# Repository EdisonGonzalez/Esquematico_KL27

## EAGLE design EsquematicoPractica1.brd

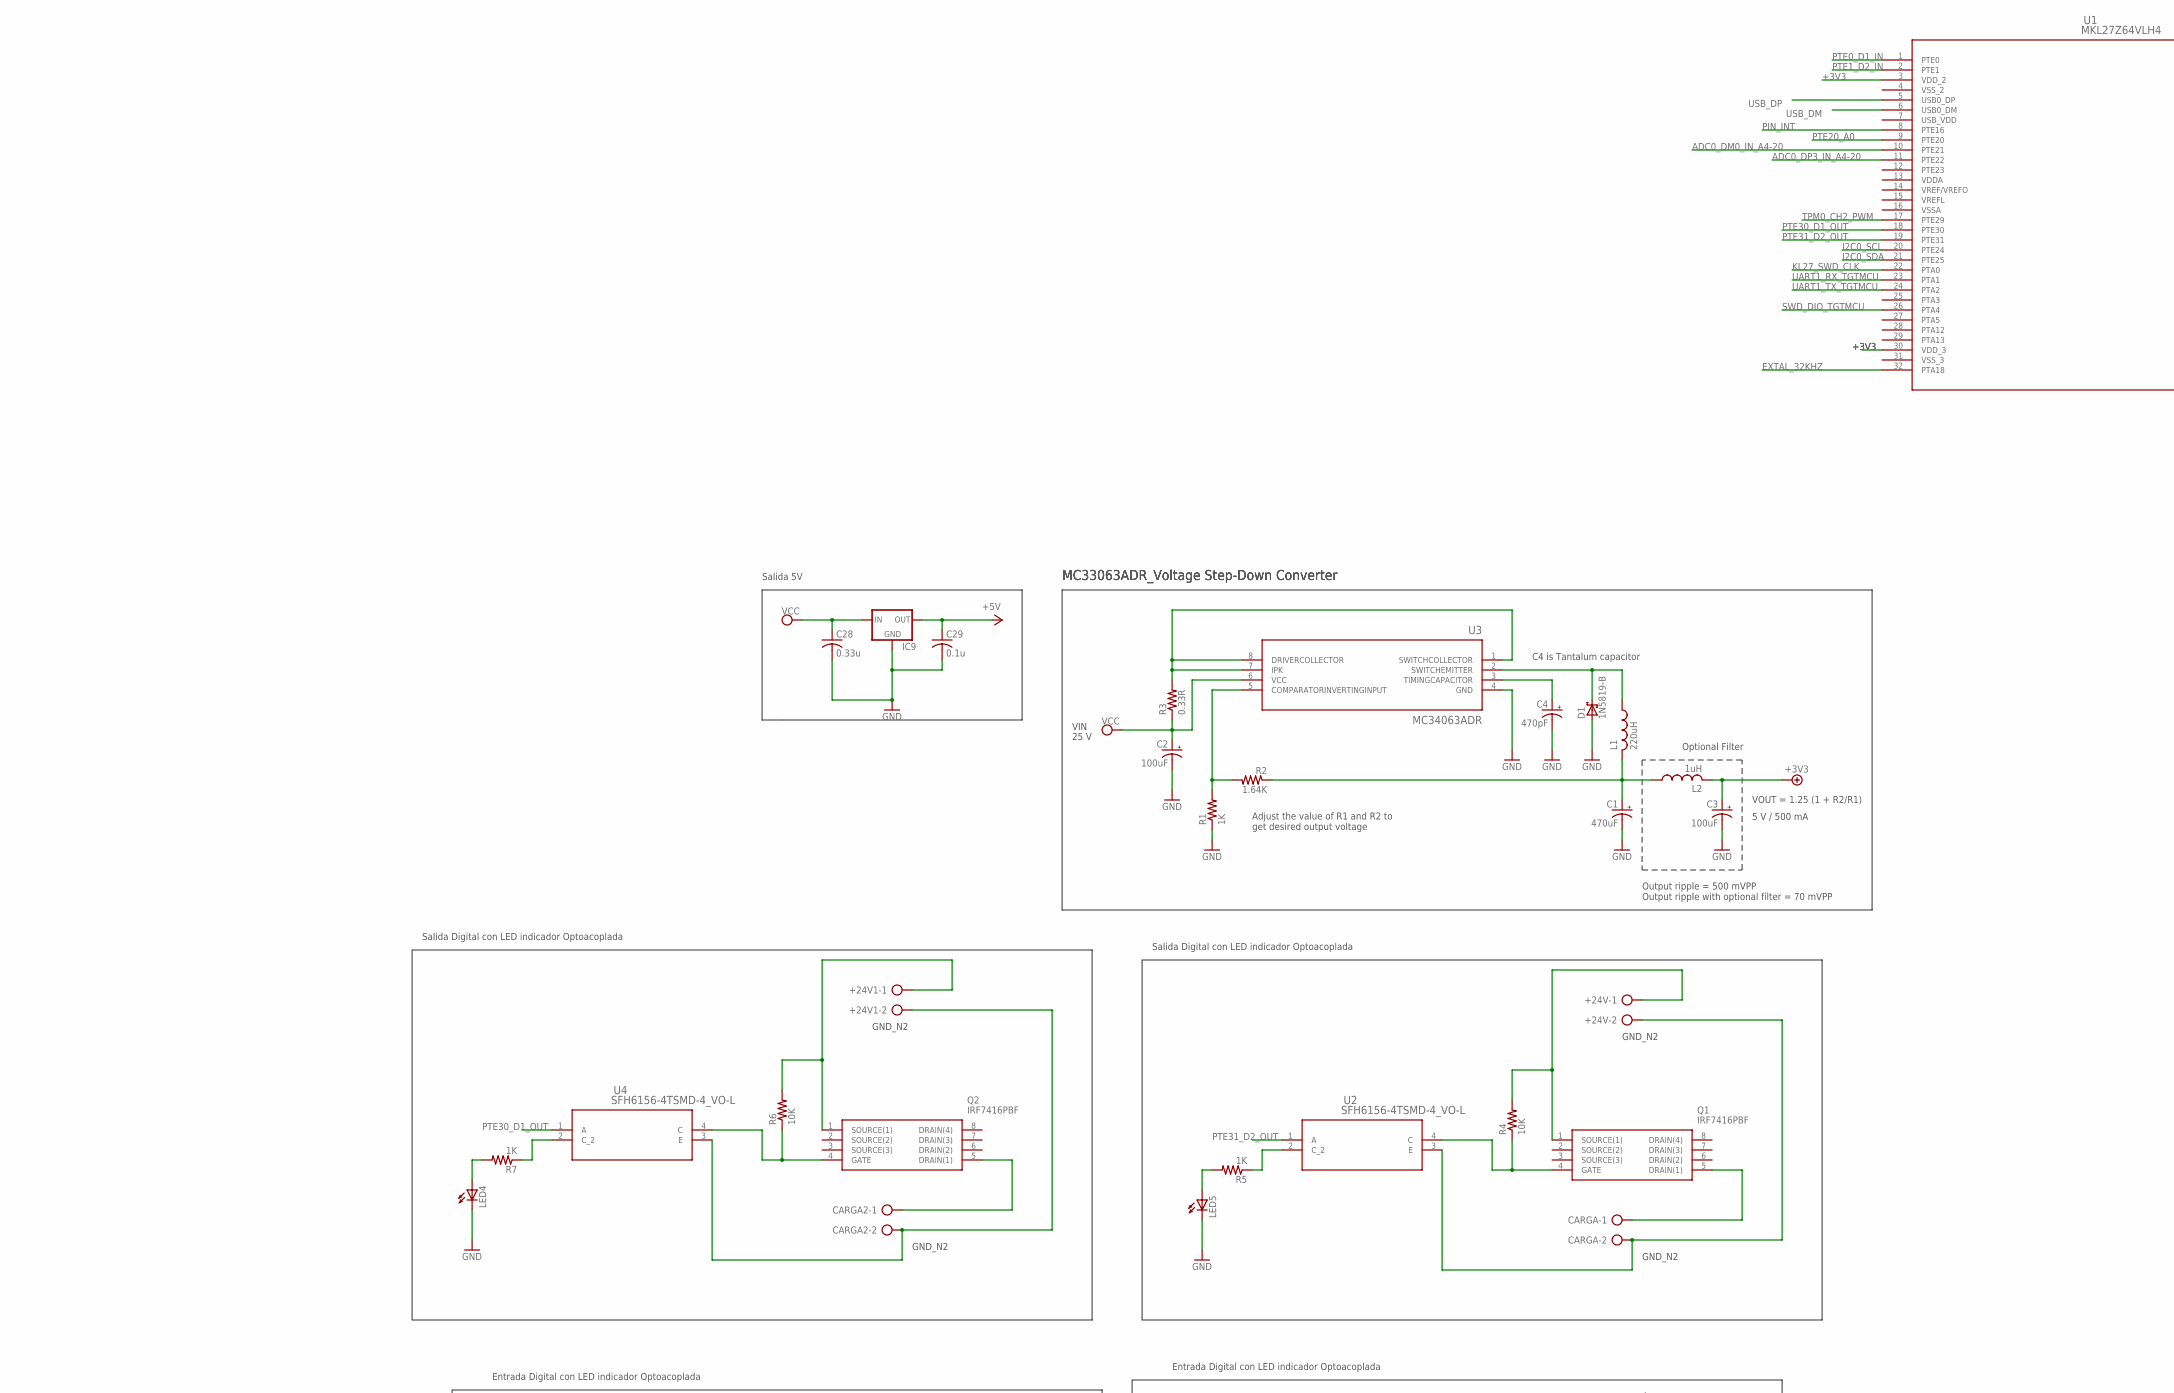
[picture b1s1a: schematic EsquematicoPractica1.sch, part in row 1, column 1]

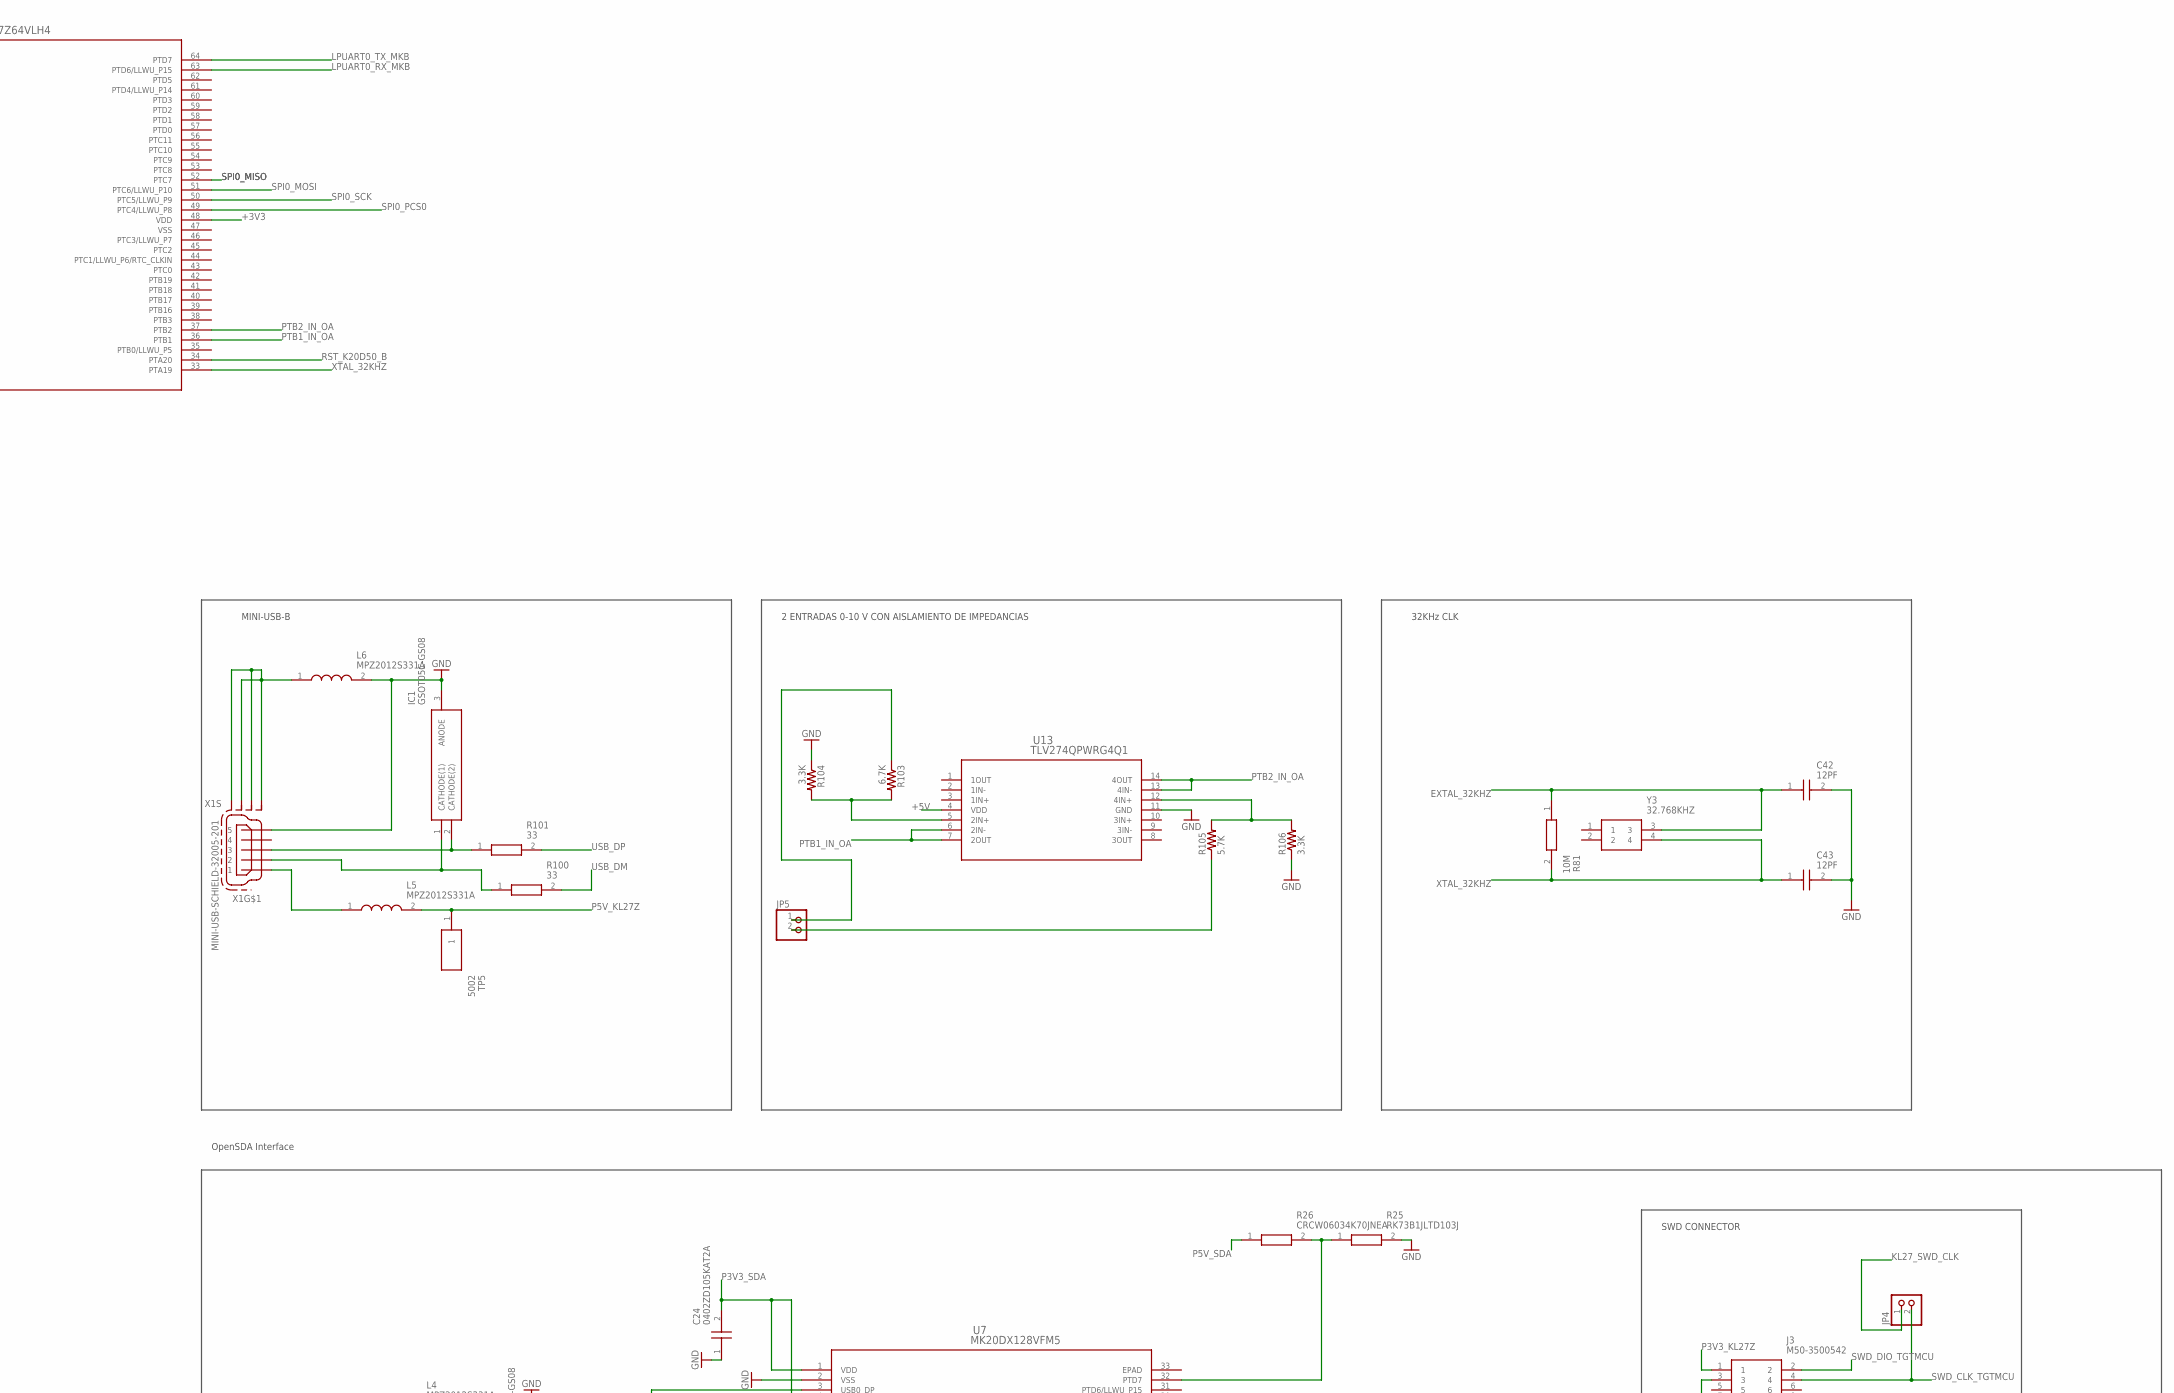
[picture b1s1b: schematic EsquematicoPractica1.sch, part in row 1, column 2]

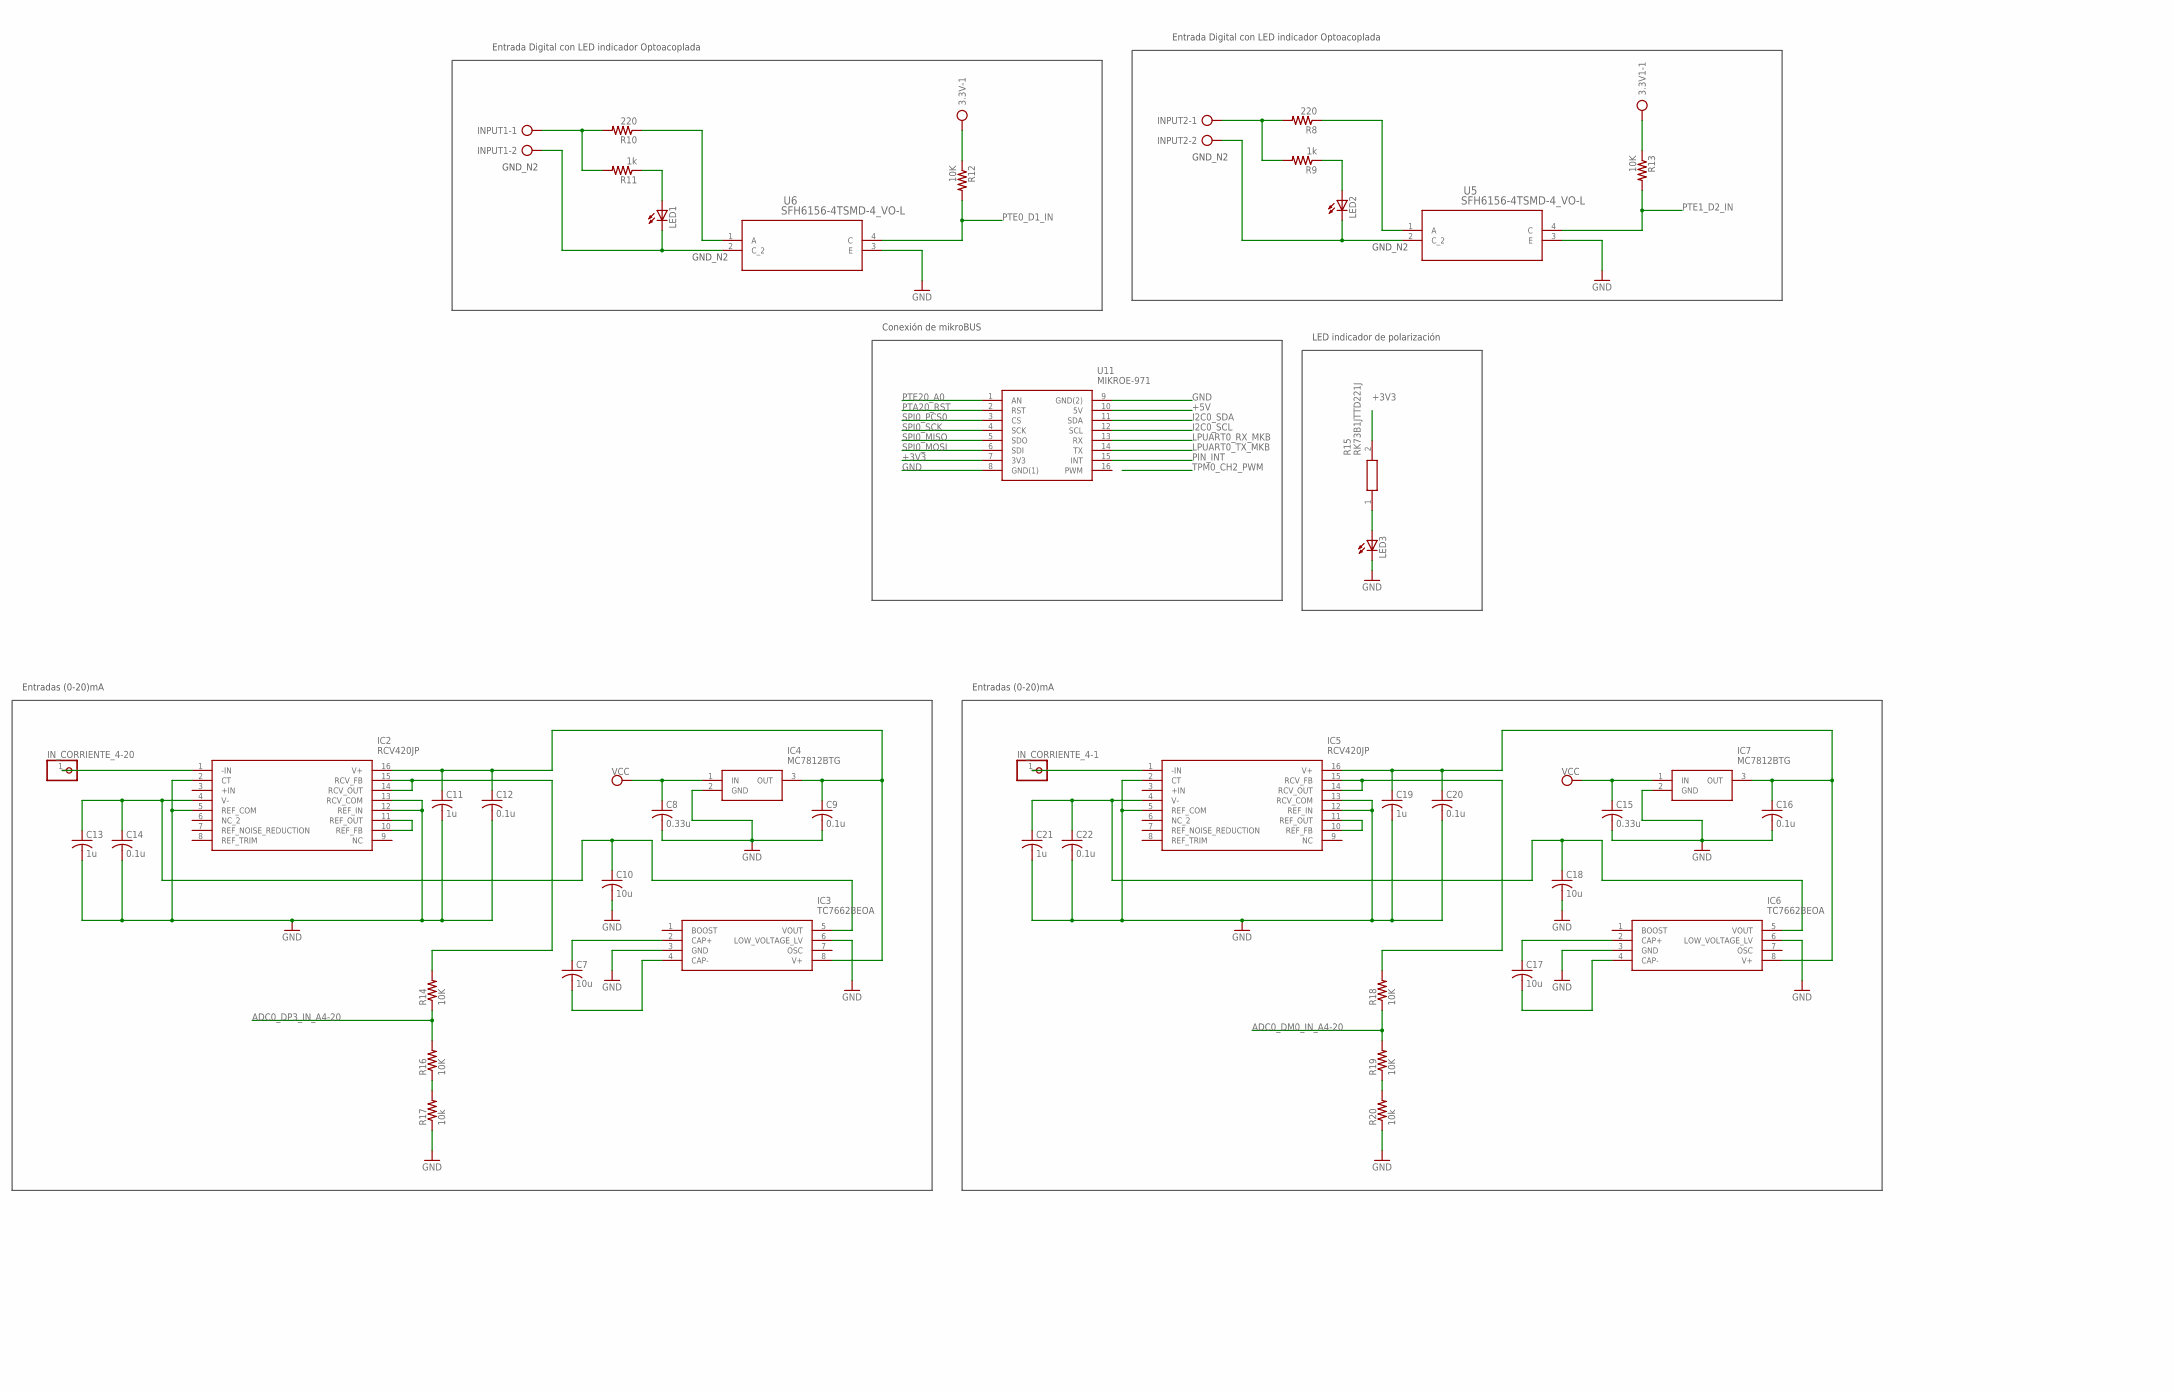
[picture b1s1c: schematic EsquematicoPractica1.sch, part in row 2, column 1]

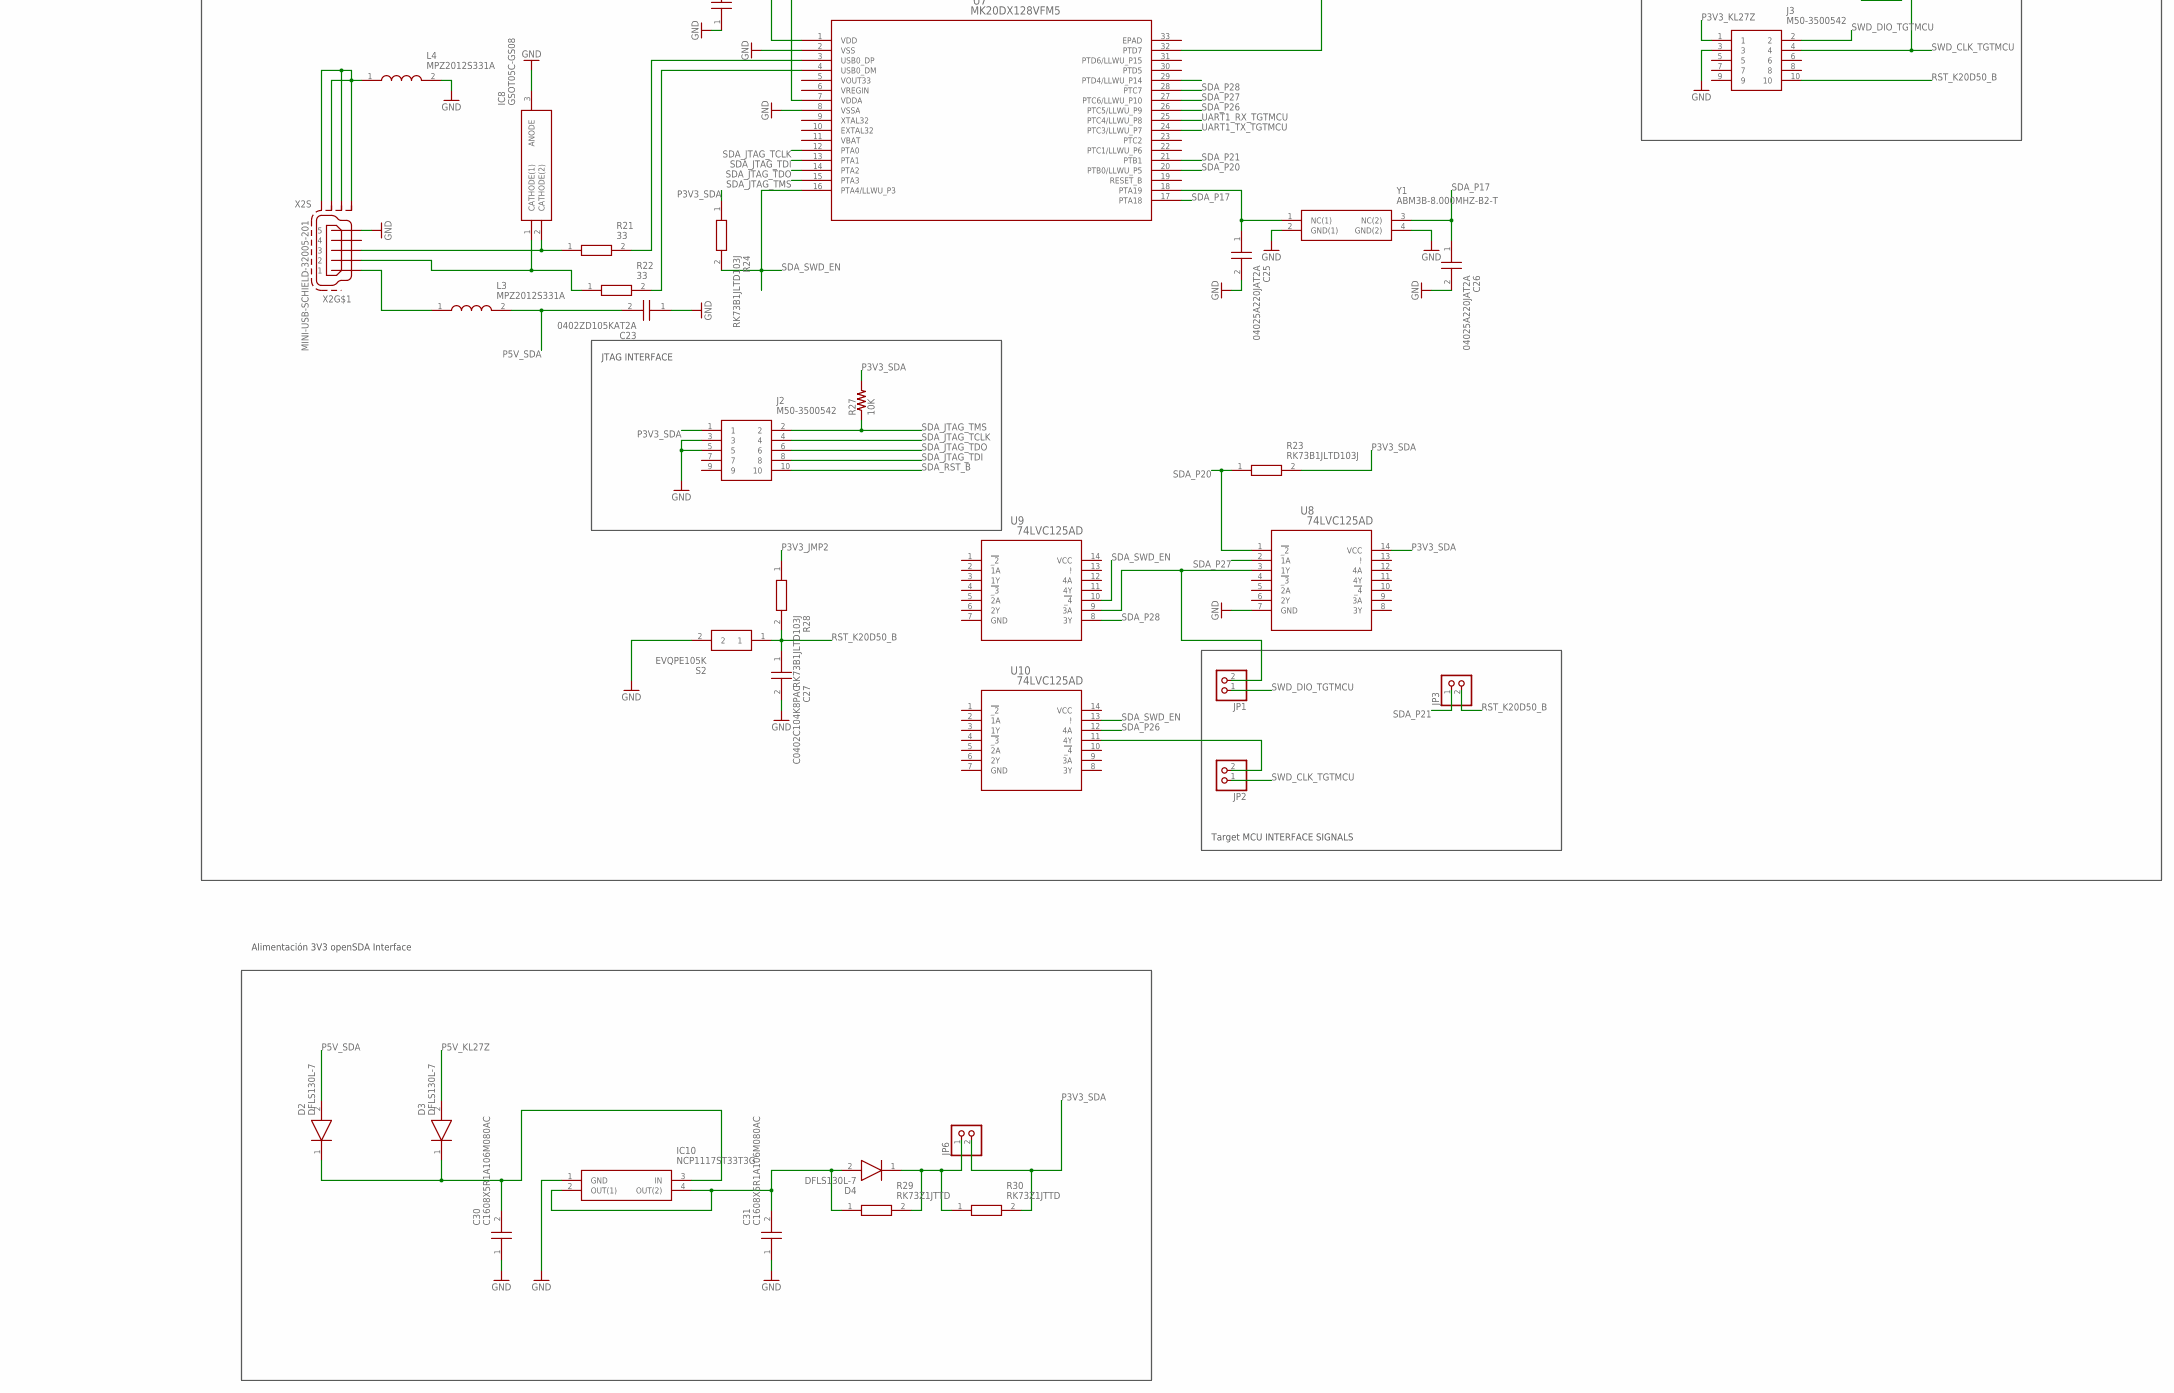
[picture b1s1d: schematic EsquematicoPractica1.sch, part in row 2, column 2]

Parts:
3.3V, 3.3V1: AK300/2
+24V, +24V1: AK300/2
C1: 470uF; E7,5-16
C2, C3: 100uF; E2,5-6E
C4: 470pF; E2,5-6E
C7, C10, C17, C18: 10u; C0805
C8, C15, C28: 0.33u; C0805
C9, C12, C14, C16, C20, C22, C29: 0.1u; C0805
C11, C13, C19, C21: 1u; C0805
C23, C24: 0402ZD105KAT2A; CAPC1005X56N
C25, C26: 04025A220JAT2A; CAPC1005X56N
C27: C0402C104K8PAC; CAPC1005X55N
C30, C31: C1608X5R1A106M080AC; CAPC1608X80N
C42, C43: 12PF; CAPC1005X55N
CARGA, CARGA2: AK300/2
D1: 1N5819-B; DO41-7.6
D2, D3, D4: DFLS130L-7; POWERDI_123
IC1, IC8: GSOT05C-GS08; SOT95P248X115-3N
IC2, IC5: RCV420JP; DIP254P762X508-16
IC3, IC6: TC7662BEOA; SOIC127P600X175-8N
IC4, IC7: MC7812BTG; TO254P482X997X2018-3P
IC9: 78XXL
IC10: NCP1117ST33T3G; SOT230P700X180-4N
INPUT1, INPUT2: AK300/2
IN_CORRIENTE_4-1, IN_CORRIENTE_4-20: PINHD-1X1; 1X01
J2, J3: M50-3500542; HDRV10W40P127_2X5_635X345X415P
JP1, JP2, JP3, JP4, JP6: PINHD-1X2/90; 1X02/90
JP5: PINHD-1X2; 1X02
L1: 220uH; L3216C
L2: 1uH; L3216C
L3, L4, L5, L6: MPZ2012S331A; INDC2012X105N
LED1, LED2, LED3, LED4, LED5: LED5MM
Q1, Q2: IRF7416PBF; SOIC127P600X175-8N
R1: 1K; M0805
R2: 1.64K; M0805
R3: 0.33R; M0805
R4, R6: 10K; 0309/12
R5, R7: 1K; 0309/12
R8: 220; 0309/12
R9, R11: 1k; 0309/12
R10: 220; 0204/7
R12, R13: 10K; 0204/7
R14, R16, R18, R19: 10K; M0805
R15: RK73B1JTTD221J; RESC1608X55N
R17, R20: 10k; M0805
R21, R22, R100, R101: 33; RESC1005X40N
R23, R24, R25, R28: RK73B1JLTD103J; RESC1608X55N
R26: CRCW06034K70JNEA; RESC1608X50N
R27: 10K; M1206
R29, R30: RK73Z1JTTD; RESC1608X55N
R81: 10M; RESC1608X55N
R103: 6.7K; M1206
R104, R106: 3.3K; M1206
R105: 5.7K; M1206
S2: EVQPE105K; EVQPE1
TP5: 5002
U1: MKL27Z64VLH4; 98ASS23234W
U2, U4, U5, U6: SFH6156-4TSMD-4_VO-L; SMD-4_VO-L
U3: MC34063ADR; D8
U7: MK20DX128VFM5; QFN-32_5X5X0.9
U8, U9, U10: 74LVC125AD; SOT108-1
U11: MIKROE-971; MIKROE-971_1
U13: TLV274QPWRG4Q1; PW14
X1, X2: MINI-USB-SCHIELD-32005-201; 32005-201
Y1: ABM3B-8.000MHZ-B2-T; ABM3B
Y3: 32.768KHZ; ABS2532768KHZT

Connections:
+3V3: R15.2, U1.3 (VDD_2), U1.30 (VDD_3), U1.48 (VDD), U11.7 (3V3)
+5V: C3.+, C29.1, IC9.OUT, L2.2, U11.10 (5V), U13.4 (VDD)
ADC0_DM0_IN_A4-20: R18.1, R19.2, U1.10 (PTE21)
ADC0_DP3_IN_A4-20: R14.1, R16.2, U1.11 (PTE22)
EXTAL_32KHZ: C42.1, R81.1, U1.32 (PTA18), Y3.3
GND: C1.-, C2.-, C3.-, C4.-, C8.2, C9.2, C10.2, C11.2, C12.2, C13.2, C14.2, C15.2, C16.2, C18.2, C19.2, C20.2, C21.2, C22.2, C24.1, C28.2, C29.2, C31.1, C42.2, C43.2, D1.A, IC1.3 (ANODE), IC2.2 (CT), IC2.5 (REF_COM), IC2.12 (REF_IN), IC2.13 (RCV_COM), IC3.3 (GND), IC3.6 (LOW_VOLTAGE_LV), IC4.2 (GND), IC5.2 (CT), IC5.5 (REF_COM), IC5.12 (REF_IN), IC5.13 (RCV_COM), IC6.3 (GND), IC6.6 (LOW_VOLTAGE_LV), IC7.2 (GND), IC8.3 (ANODE), IC9.GND, J2.3, J2.5, J3.3, L4.2, L6.2, LED3.K (C), LED4.K (C), LED5.K (C), R1.1, R17.1, R20.1, R104.1, R106.1, S2.2, U3.4 (GND), U5.3 (E), U6.3 (E), U7.2 (VSS), U7.8 (VSSA), U9.7 (GND), U10.7 (GND), U11.8 (GND(1)), U11.9 (GND(2)), U13.11 (GND), X1.5, X2.5, Y1.4 (GND(2))
I2C0_SCL: U1.20 (PTE24), U11.12 (SCL)
I2C0_SDA: U1.21 (PTE25), U11.11 (SDA)
KL27_SWD_CLK: JP4.1, U1.22 (PTA0)
LPUART0_RX_MKB: U1.63 (PTD6/LLWU_P15), U11.13 (RX)
LPUART0_TX_MKB: U1.64 (PTD7), U11.14 (TX)
unnamed: Q1.4 (GATE), R4.1, U2.4 (C)
unnamed: D1.C, L1.1, U3.2 (SWITCHEMITTER)
unnamed: C1.+, L1.2, L2.1, R2.1, Y1.2 (GND(1))
unnamed: C4.+, C25.2, U3.3 (TIMINGCAPACITOR)
unnamed: R5.1, U2.2 (C_2)
unnamed: CARGA.1, Q1.5 (DRAIN(1))
unnamed: C26.2, R1.2, R2.2, U3.5 (COMPARATORINVERTINGINPUT)
unnamed: +24V.1, Q1.1 (SOURCE(1)), R4.2
unnamed: R3.2, U3.1 (SWITCHCOLLECTOR), U3.7 (IPK), U3.8 (DRIVERCOLLECTOR)
unnamed: +24V.2, CARGA.2, U2.3 (E)
unnamed: Q2.4 (GATE), R6.1, U4.4 (C)
unnamed: +24V1.1, Q2.1 (SOURCE(1)), R6.2
unnamed: R7.1, U4.2 (C_2)
unnamed: CARGA2.1, Q2.5 (DRAIN(1))
unnamed: +24V1.2, CARGA2.2, U4.3 (E)
unnamed: INPUT2.1, R8.2, R9.2
unnamed: R8.1, U5.1 (A)
unnamed: LED2.A, R9.1
unnamed: JP5.1, R103.1
unnamed: 3.3V1.1, R13.1
unnamed: INPUT1.1, R10.2, R11.2
unnamed: R10.1, U6.1 (A)
unnamed: 3.3V.1, R12.1
unnamed: LED1.A, R11.1
unnamed: INPUT1.2, INPUT2.2, LED1.K (C), LED2.K (C), U5.2 (C_2), U6.2 (C_2)
unnamed: LED3.A, R15.1
unnamed: C7.1, IC3.2 (CAP+)
unnamed: JP5.2, R105.1
unnamed: C9.1, C11.1, C12.1, IC2.16 (V+), IC3.8 (V+), IC4.3 (OUT)
unnamed: C7.2, IC3.4 (CAP-)
unnamed: IC2.10 (REF_FB), IC2.11 (REF_OUT)
unnamed: C30.2, D2.1 (K), D3.1 (K), IC10.3 (IN)
unnamed: C10.1, C13.1, C14.1, IC2.4 (V-), IC3.5 (VOUT)
unnamed: R16.1, R17.2
unnamed: IC2.14 (RCV_OUT), IC2.15 (RCV_FB), R14.2
unnamed: IC2.1 (-IN), IN_CORRIENTE_4-20.1
unnamed: C16.1, C19.1, C20.1, IC5.16 (V+), IC6.8 (V+), IC7.3 (OUT)
unnamed: C17.1, IC6.2 (CAP+)
unnamed: C17.2, IC6.4 (CAP-)
unnamed: C18.1, C21.1, C22.1, IC5.4 (V-), IC6.5 (VOUT)
unnamed: IC5.10 (REF_FB), IC5.11 (REF_OUT)
unnamed: IC5.14 (RCV_OUT), IC5.15 (RCV_FB), R18.2
unnamed: C31.2, D4.2 (A), IC10.2 (OUT(1)), IC10.4 (OUT(2)), R29.1
unnamed: R19.1, R20.2
unnamed: IC5.1 (-IN), IN_CORRIENTE_4-1.1
unnamed: IC8.2 (CATHODE(2)), R21.1, X2.3
unnamed: L3.1, X2.1
unnamed: IC8.1 (CATHODE(1)), R22.1, X2.2
unnamed: L4.1, X2.M1 (S1), X2.M2 (S2), X2.M3 (S3), X2.M4 (S4)
unnamed: C25.1, U7.18 (PTA19), Y1.1 (NC(1))
unnamed: JP2.2, U10.11 (4Y)
unnamed: R25.1, R26.2, U7.32 (PTD7)
unnamed: JP1.2, U8.3 (1Y), U9.9 (3A)
unnamed: LED4.A, R7.2
unnamed: LED5.A, R5.2
unnamed: D4.1 (K), JP6.1, R29.2, R30.1
unnamed: IC1.2 (CATHODE(2)), R101.1, X1.3
unnamed: L5.1, X1.1
unnamed: IC1.1 (CATHODE(1)), R100.1, X1.2
unnamed: L6.1, X1.M1 (S1), X1.M2 (S2), X1.M3 (S3), X1.M4 (S4)
unnamed: R103.2, R104.2, U13.5 (2IN+)
unnamed: R105.2, R106.2, U13.12 (4IN+)
P3V3_JMP2: R28.1
P3V3_KL27Z: J3.1
P3V3_SDA: C24.2, J2.1, JP6.2, R23.2, R24.1, R27.2, R30.2, U7.1 (VDD), U7.7 (VDDA), U8.14 (VCC)
P5V_KL27Z: D3.2 (A), L5.2, TP5.1
P5V_SDA: C23.2, D2.2 (A), L3.2, R26.1
PIN_INT: U1.8 (PTE16), U11.15 (INT)
PTA20_RST: U11.2 (RST)
PTB1_IN_OA: U1.36 (PTB1), U13.6 (2IN-), U13.7 (2OUT)
PTB2_IN_OA: U1.37 (PTB2), U13.13 (4IN-), U13.14 (4OUT)
PTE0_D1_IN: R12.2, U1.1 (PTE0), U6.4 (C)
PTE1_D2_IN: R13.2, U1.2 (PTE1), U5.4 (C)
PTE20_A0: U1.9 (PTE20), U11.1 (AN)
PTE30_D1_OUT: U1.18 (PTE30), U4.1 (A)
PTE31_D2_OUT: U1.19 (PTE31), U2.1 (A)
RST_K20D50_B: C27.1, J3.10, JP3.2, R28.2, S2.1, U1.34 (PTA20)
SDA_JTAG_TCLK: J2.4, U7.12 (PTA0)
SDA_JTAG_TDI: J2.8, U7.13 (PTA1)
SDA_JTAG_TDO: J2.6, U7.14 (PTA2)
SDA_JTAG_TMS: J2.2, R27.1, U7.15 (PTA3)
SDA_P17: C26.1, U7.17 (PTA18), Y1.3 (NC(2))
SDA_P20: R23.1, U7.20 (PTB0/LLWU_P5), U8.1 (!_2)
SDA_P21: JP3.1, U7.21 (PTB1)
SDA_P26: U7.26 (PTC5/LLWU_P9), U10.12 (4A)
SDA_P27: U7.27 (PTC6/LLWU_P10), U8.2 (1A)
SDA_P28: U7.28 (PTC7), U9.8 (3Y)
SDA_RST_B: J2.10
SDA_SWD_EN: R24.2, U7.16 (PTA4/LLWU_P3), U9.10 (!_4), U10.13 (!)
SPI0_MISO: U1.52 (PTC7), U11.5 (SDO)
SPI0_MOSI: U1.51 (PTC6/LLWU_P10), U11.6 (SDI)
SPI0_PCS0: U1.49 (PTC4/LLWU_P8), U11.3 (CS)
SPI0_SCK: U1.50 (PTC5/LLWU_P9), U11.4 (SCK)
SWD_CLK_TGTMCU: J3.4, JP2.1, JP4.2
SWD_DIO_TGTMCU: J3.2, JP1.1, U1.26 (PTA4)
TPM0_CH2_PWM: U1.17 (PTE29)
UART1_RX_TGTMCU: U1.23 (PTA1), U7.25 (PTC4/LLWU_P8)
UART1_TX_TGTMCU: U1.24 (PTA2), U7.24 (PTC3/LLWU_P7)
USB_DM: R100.2, U1.6 (USB0_DM)
USB_DM1: R22.2, U7.4 (USB0_DM)
USB_DP: R101.2, U1.5 (USB0_DP)
USB_DP1: R21.2, U7.3 (USB0_DP)
USB_VDD: U1.7 (USB_VDD)
VBAT: U7.11 (VBAT)
VCC: C2.+, C8.1, C15.1, C28.1, IC4.1 (IN), IC7.1 (IN), IC9.IN, R3.1, U3.6 (VCC), U9.14 (VCC), U10.14 (VCC)
VDDA: U1.13 (VDDA)
VREF/VREFO: U1.14 (VREF/VREFO)
VREFL: U1.15 (VREFL)
VSS: U1.47 (VSS)
VSSA: U1.16 (VSSA)
VSS_2: U1.4 (VSS_2)
VSS_3: U1.31 (VSS_3)
XTAL_32KHZ: C43.1, R81.2, U1.33 (PTA19), Y3.4

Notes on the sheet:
25 V
5 V / 500 mA
Optional Filter
VOUT = 1.25 (1 + R2/R1)
MC33063ADR_Voltage Step-Down Converter
VIN
Adjust the value of R1 and R2 to get desired output voltage
Output ripple = 500 mVPP Output ripple with optional filter = 70 mVPP
C4 is Tantalum capacitor
Salida Digital con LED indicador Optoacoplada
Entrada Digital con LED indicador Optoacoplada
LED indicador de polarización
MINI-USB-B
32KHz CLK
2 ENTRADAS 0-10 V CON AISLAMIENTO DE IMPEDANCIAS
Conexión de mikroBUS
Entradas (0-20)mA
Target MCU INTERFACE SIGNALS
JTAG INTERFACE
SWD CONNECTOR
OpenSDA Interface
Salida 5V
GND_N2
Alimentación 3V3 openSDA Interface

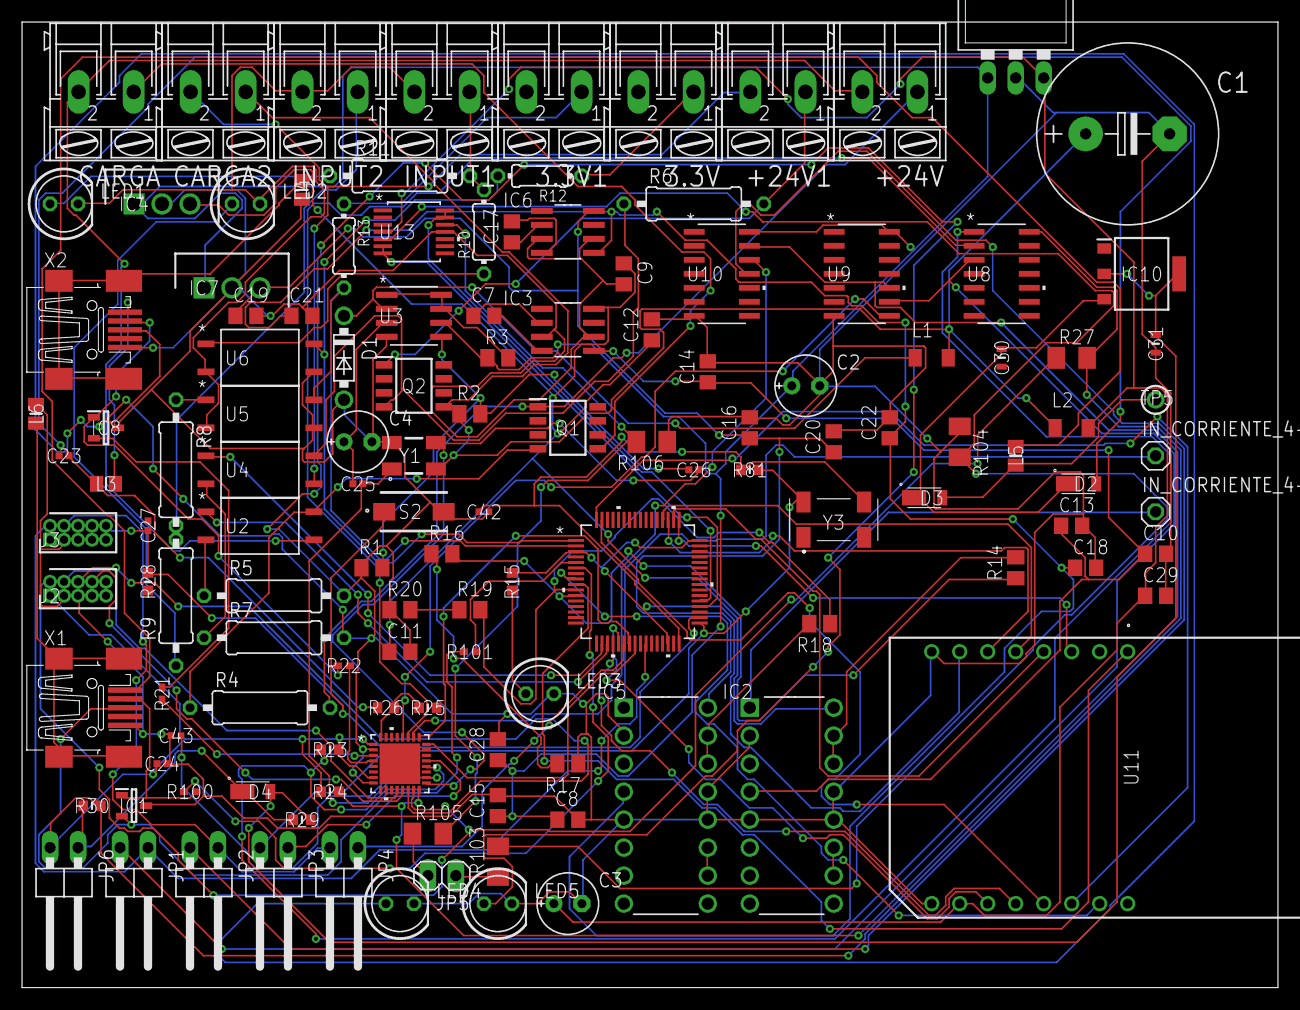
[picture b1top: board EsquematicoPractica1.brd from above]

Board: 2 copper layers, 114.0 x 87.6 mm, 131 parts (0 on the bottom side), 110 nets.

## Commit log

2018-03-13 Primer avance - práctica 1
    Fuente switcheada, entradas y salidas optoacopladas
2018-03-13 [prueba]
2018-03-13 +Led Polarización
    Se organizó la fuente regulada con los valores de resistencias R1,R2 que garantizan un voltaje de salida de 3.3V (3V3) y se agrego un led de polarización, esto es, cuando la KL27 este energizada, un 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
2018-03-13 [Code] Mini USB
2018-03-13 [Code] Mini-USB-B finished
2018-03-13 [Code] JTAG interface without pin connections
2018-03-14 [Code] Cristal circuit finished and
2018-03-14 [code] TLV274QPWRG4Q1
2018-03-14 [rafactyor] GND Rename
2018-03-14 RST & LED Polarización PERFECTO
    Verificar las resistencias usadas para las entradas y salidad además de empezar a hacer conexiones directamente con la KL27z
2018-03-14 [Refactor] Labels and Resistors update
2018-03-14 [Refactor] Restore circuits sheet
2018-03-14 Update merge sheet 2 into sheet 1
2018-03-14 Update resistors
2018-03-14 con mikroBUS
    El esquema del mikroBUS aun no es similar al del profesor pero esta a la medida.
2018-03-19 Con dos entradas de 0-4mA.
    Esta completo falta revisar los pines y conectarlos a la KL.
2018-03-19 [Code] SDA_INTERFACE
2018-03-20 Con todo
    Revisar un montaje de 5V a 3V3 en openSDA interface, algunas resistencias y terminar de conectar el open SDA Interface con la KL.
2018-03-20 Todo falta revisar conexiones
    Autoroutear y organizar
2018-03-21 [Code] Full Esquemático
2018-03-21 Esquemático full ahora sí
2018-03-21 Esquemático Full Ahora Sí de Verdad
    Valores y conexiones perfectas.
2018-03-21 Reset master
2018-03-21 El primer Board PCB
    Aqui se encuentra el PCB sin su correcto enrutamiento.
2018-03-21 [Commit] PCB Optional
2018-03-21 Enrutado falta el MikroBus
    Casi enrutado todo
2018-03-21 Practica 1 - Total Entrega
    PCB + Esquematico
2018-03-21 Práctica 1 - Entregada y Corregida
    Con todos sus valores adecuados, esquematico y PCB, solo faltó ROUTEAR adecuadamente con criterios como estabilidad en las fuentes y demas.
